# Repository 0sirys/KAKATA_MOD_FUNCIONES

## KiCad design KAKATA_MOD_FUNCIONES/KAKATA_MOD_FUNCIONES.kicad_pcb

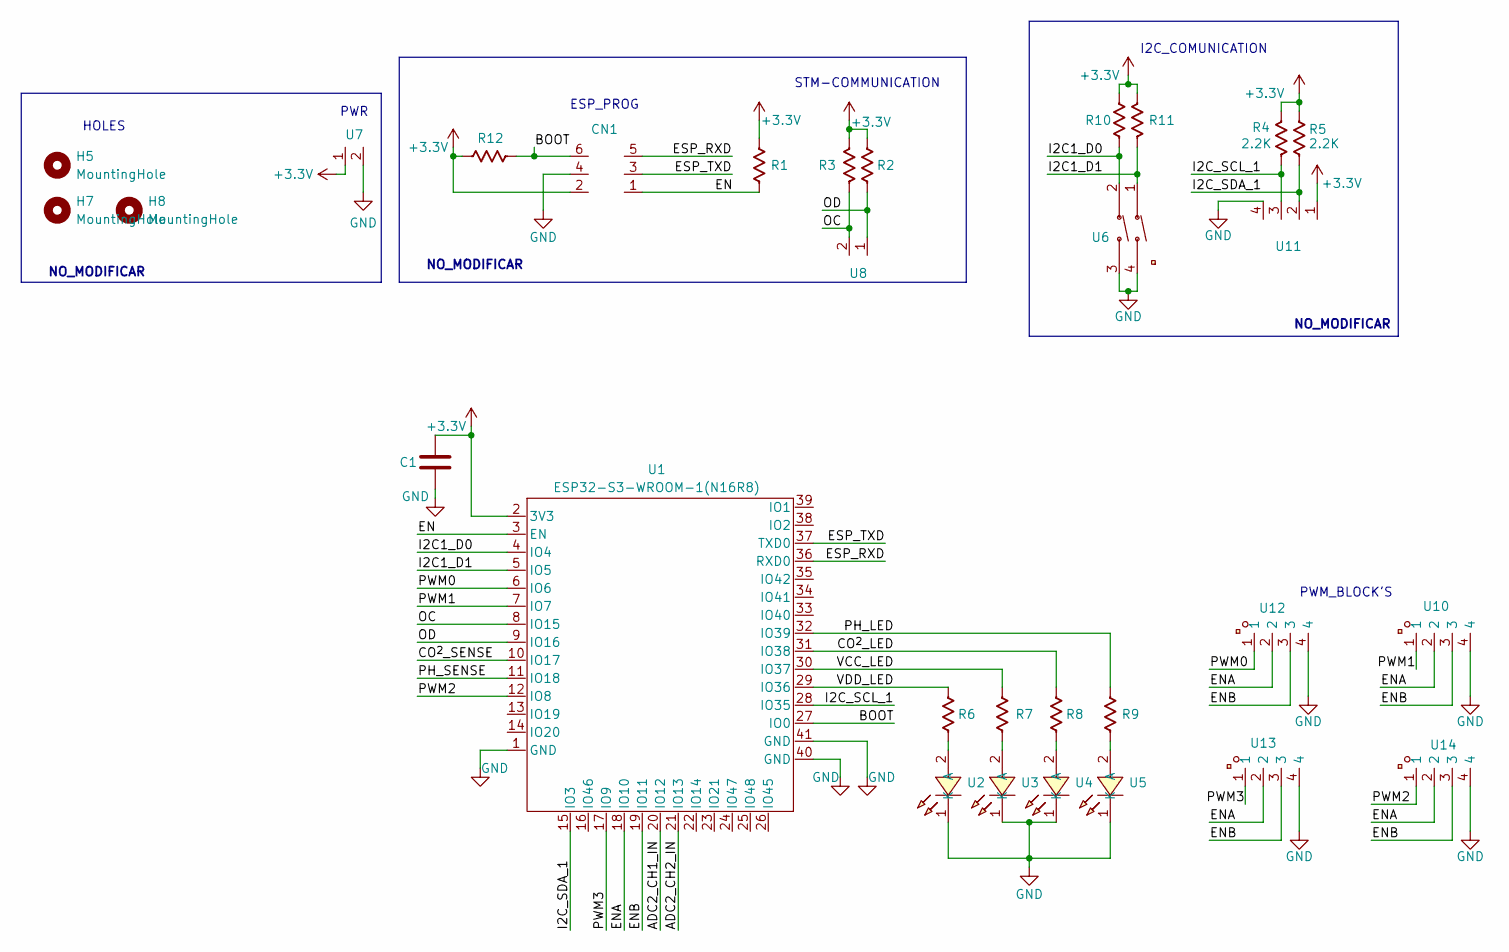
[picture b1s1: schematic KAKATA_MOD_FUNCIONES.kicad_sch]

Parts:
C1: C_0603; C_0603_1608Metric
CN1: HX JN1.27-2X3 TP H4.9; CONN-SMD_6P-P1.27-LS5.8; LCSC Part C42372553
H5, H7, H8: MountingHole; MountingHole_2.2mm_M2
R1, R12: 10K; R_0603_1608Metric
R2, R3, R6, R7, R8, R9, R10, R11: R_0603; R_0603_1608Metric
R4, R5: 2.2K; R_0603_1608Metric
U1: ESP32-S3-WROOM-1(N16R8); WIRELM-SMD_ESP32-S3-WROOM-1; LCSC Part C2913202
U2, U3, U4, U5: PSC-1608U52GC-G4; LED0603-RD_GREEN; LCSC Part C22371297
U6: SMQP-02R-TP; SW-TH_4P-P2.54_SMQP-02R-TP; LCSC Part C5299482
U7, U8: DB125-3.5-2P-GN-S; CONN-TH_2P-P3.50_L7.4-W7.0; LCSC Part C466970
U10, U11, U12, U13, U14: DB125-2.54-4P-GN; CONN-TH_DB125-2.54-4P-GN; LCSC Part C918122

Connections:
+3.3V: C1.2, CN1.2, R1.1, R2.1, R3.1, R4.1, R5.1, R10.2, R11.2, R12.2, U1.2 (3V3), U7.1, U11.1
/ADC2_CH1_IN: U1.20 (IO12)
/ADC2_CH2_IN: U1.21 (IO13)
/BOOT: CN1.6, R12.1, U1.27 (IO0)
/CO^{2}_LED: R8.1, U1.31 (IO38)
/CO^{2}_SENSE: U1.10 (IO17)
/EN: CN1.1, R1.2, U1.3 (EN)
/ENA: U1.18 (IO10), U10.2, U12.2, U13.2, U14.2
/ENB: U1.19 (IO11), U10.3, U12.3, U13.3, U14.3
/ESP_RXD: CN1.5, U1.36 (RXD0)
/ESP_TXD: CN1.3, U1.37 (TXD0)
/I2C1_D0: R10.1, U1.4 (IO4), U6.2
/I2C1_D1: R11.1, U1.5 (IO5), U6.1
/I2C_SCL_1: R4.2, U1.28 (IO35), U11.3
/I2C_SDA_1: R5.2, U1.15 (IO3), U11.2
/OC: R3.2, U1.8 (IO15), U8.2
/OD: R2.2, U1.9 (IO16), U8.1
/PH_LED: R9.1, U1.32 (IO39)
/PH_SENSE: U1.11 (IO18)
/PWM0: U1.6 (IO6), U12.1
/PWM1: U1.7 (IO7), U10.1
/PWM2: U1.12 (IO8), U14.1
/PWM3: U1.17 (IO9), U13.1
/VCC_LED: R7.1, U1.30 (IO37)
/VDD_LED: R6.1, U1.29 (IO36)
GND: C1.1, CN1.4, U1.1 (GND), U1.40 (GND), U1.41 (GND), U2.1 (K), U3.1 (K), U4.1 (K), U5.1 (K), U6.3, U6.4, U7.2, U10.4, U11.4, U12.4, U13.4, U14.4
unnamed: R6.2, U2.2 (A)
unnamed: R7.2, U3.2 (A)
unnamed: R8.2, U4.2 (A)
unnamed: R9.2, U5.2 (A)

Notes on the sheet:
STM-COMMUNICATION
NO_MODIFICAR
ESP_PROG
PWR
HOLES
PWM_BLOCK'S
I2C_COMUNICATION

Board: 4 copper layers, 30 parts (0 on the bottom side), 26 nets, no tracks yet.

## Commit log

2025-12-11 Primer commit
2025-12-13 segundo commit
2025-12-14 Base hecha
2025-12-14 hot_fix_Done
